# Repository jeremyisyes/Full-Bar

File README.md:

# Full-Bar
 40% keyboard with an encoder, full-sized shifts, full-sized enter, and a 10u spacebar.

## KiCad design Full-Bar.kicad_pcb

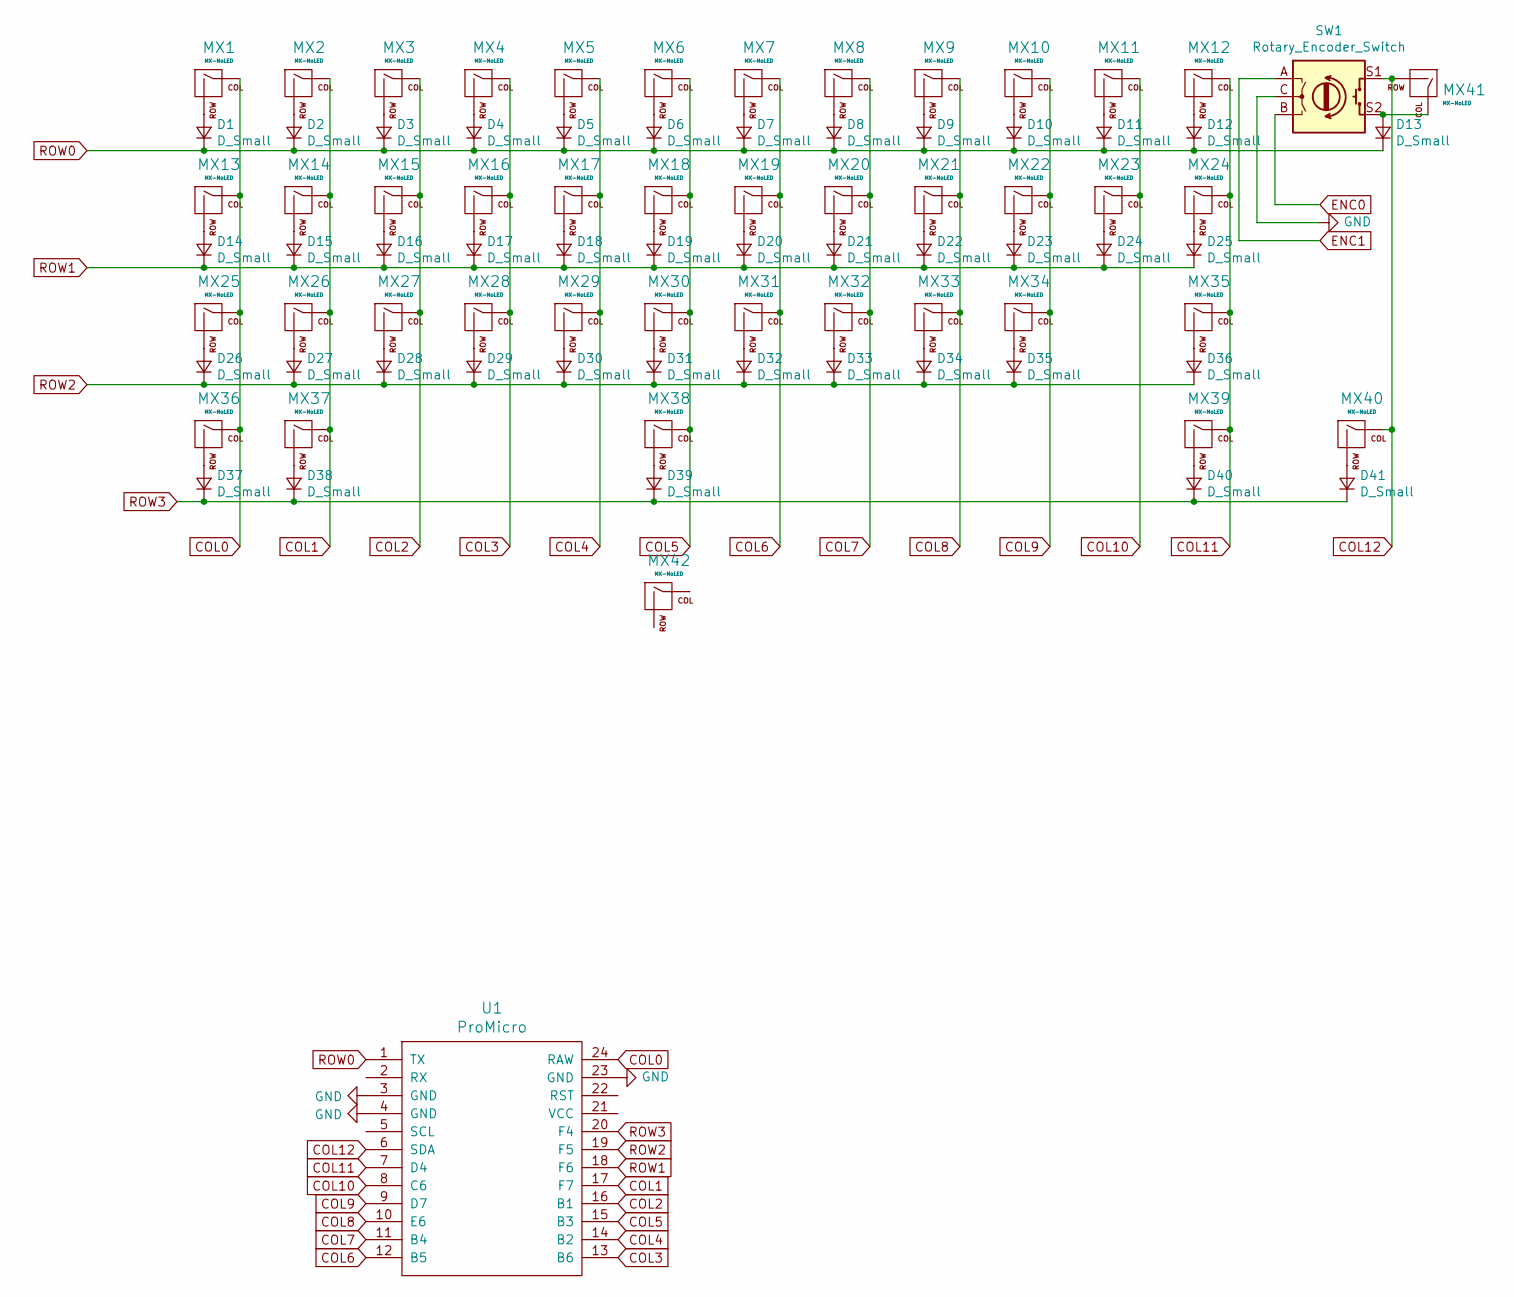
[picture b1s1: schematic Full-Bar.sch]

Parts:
D1, D2, D3, D4, D5, D6, D7, D8, D9, D10, D11, D12, D13, D14, D15, D16, D17, D18, D19, D20, D21, D22, D23, D24, D25, D26, D27, D28, D29, D30, D31, D32, D33, D34, D35, D36, D37, D38, D39, D40, D41: D_Small; D_A-405_P7.62mm_Horizontal
MX1, MX12: MX-NoLED; MX-1.5U-NoLED
MX2, MX3, MX4, MX5, MX6, MX7, MX8, MX9, MX10, MX11, MX14, MX15, MX16, MX17, MX18, MX19, MX20, MX21, MX22, MX23, MX26, MX27, MX28, MX29, MX30, MX31, MX32, MX33, MX34, MX36, MX37, MX39, MX40, MX41: MX-NoLED; MX-1U-NoLED
MX13: MX-NoLED; MX-1.75U-NoLED
MX24, MX25: MX-NoLED; MX-2.25U-NoLED
MX35: MX-NoLED; MX-2.75U-NoLED
MX38: MX-NoLED; MX-10U-ReversedStabilizers-NoLED
MX42: MX-NoLED; MX-7U-ReversedStabilizers-NoLED
SW1: Rotary_Encoder_Switch; RotaryEncoder_Alps_EC11E-Switch_Vertical_H20mm
U1: ProMicro

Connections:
COL0: MX1.1 (COL), MX13.1 (COL), MX25.1 (COL), MX36.1 (COL), U1.24 (RAW)
COL1: MX2.1 (COL), MX14.1 (COL), MX26.1 (COL), MX37.1 (COL), U1.17 (F7)
COL2: MX3.1 (COL), MX15.1 (COL), MX27.1 (COL), U1.16 (B1)
COL3: MX4.1 (COL), MX16.1 (COL), MX28.1 (COL), U1.13 (B6)
COL4: MX5.1 (COL), MX17.1 (COL), MX29.1 (COL), U1.14 (B2)
COL5: MX6.1 (COL), MX18.1 (COL), MX30.1 (COL), MX38.1 (COL), U1.15 (B3)
COL6: MX7.1 (COL), MX19.1 (COL), MX31.1 (COL), U1.12 (B5)
COL7: MX8.1 (COL), MX20.1 (COL), MX32.1 (COL), U1.11 (B4)
COL8: MX9.1 (COL), MX21.1 (COL), MX33.1 (COL), U1.10 (E6)
COL9: MX10.1 (COL), MX22.1 (COL), MX34.1 (COL), U1.9 (D7)
COL10: MX11.1 (COL), MX23.1 (COL), U1.8 (C6)
COL11: MX12.1 (COL), MX24.1 (COL), MX35.1 (COL), MX39.1 (COL), U1.7 (D4)
COL12: MX40.1 (COL), MX41.2 (ROW), SW1.S1, U1.6 (SDA)
GND: SW1.C, U1.3 (GND), U1.4 (GND), U1.23 (GND)
unnamed: D1.2 (A), MX1.2 (ROW)
unnamed: D2.2 (A), MX2.2 (ROW)
unnamed: D3.2 (A), MX3.2 (ROW)
unnamed: D4.2 (A), MX4.2 (ROW)
unnamed: D5.2 (A), MX5.2 (ROW)
unnamed: D6.2 (A), MX6.2 (ROW)
unnamed: D7.2 (A), MX7.2 (ROW)
unnamed: D8.2 (A), MX8.2 (ROW)
unnamed: D9.2 (A), MX9.2 (ROW)
unnamed: D10.2 (A), MX10.2 (ROW)
unnamed: D11.2 (A), MX11.2 (ROW)
unnamed: D12.2 (A), MX12.2 (ROW)
unnamed: D13.2 (A), MX41.1 (COL), SW1.S2
unnamed: D14.2 (A), MX13.2 (ROW)
unnamed: D15.2 (A), MX14.2 (ROW)
unnamed: D16.2 (A), MX15.2 (ROW)
unnamed: D17.2 (A), MX16.2 (ROW)
unnamed: D18.2 (A), MX17.2 (ROW)
unnamed: D19.2 (A), MX18.2 (ROW)
unnamed: D20.2 (A), MX19.2 (ROW)
unnamed: D21.2 (A), MX20.2 (ROW)
unnamed: D22.2 (A), MX21.2 (ROW)
unnamed: D23.2 (A), MX22.2 (ROW)
unnamed: D24.2 (A), MX23.2 (ROW)
unnamed: D25.2 (A), MX24.2 (ROW)
unnamed: D26.2 (A), MX25.2 (ROW)
unnamed: D27.2 (A), MX26.2 (ROW)
unnamed: D28.2 (A), MX27.2 (ROW)
unnamed: D29.2 (A), MX28.2 (ROW)
unnamed: D30.2 (A), MX29.2 (ROW)
unnamed: D31.2 (A), MX30.2 (ROW)
unnamed: D32.2 (A), MX31.2 (ROW)
unnamed: D33.2 (A), MX32.2 (ROW)
unnamed: D34.2 (A), MX33.2 (ROW)
unnamed: D35.2 (A), MX34.2 (ROW)
unnamed: D36.2 (A), MX35.2 (ROW)
unnamed: D37.2 (A), MX36.2 (ROW)
unnamed: D38.2 (A), MX37.2 (ROW)
unnamed: D39.2 (A), MX38.2 (ROW)
unnamed: D40.2 (A), MX39.2 (ROW)
unnamed: D41.2 (A), MX40.2 (ROW)
ROW0: D1.1 (K), D2.1 (K), D3.1 (K), D4.1 (K), D5.1 (K), D6.1 (K), D7.1 (K), D8.1 (K), D9.1 (K), D10.1 (K), D11.1 (K), D12.1 (K), D13.1 (K), U1.1 (TX)
ROW1: D14.1 (K), D15.1 (K), D16.1 (K), D17.1 (K), D18.1 (K), D19.1 (K), D20.1 (K), D21.1 (K), D22.1 (K), D23.1 (K), D24.1 (K), D25.1 (K), U1.18 (F6)
ROW2: D26.1 (K), D27.1 (K), D28.1 (K), D29.1 (K), D30.1 (K), D31.1 (K), D32.1 (K), D33.1 (K), D34.1 (K), D35.1 (K), D36.1 (K), U1.19 (F5)
ROW3: D37.1 (K), D38.1 (K), D39.1 (K), D40.1 (K), D41.1 (K), U1.20 (F4)

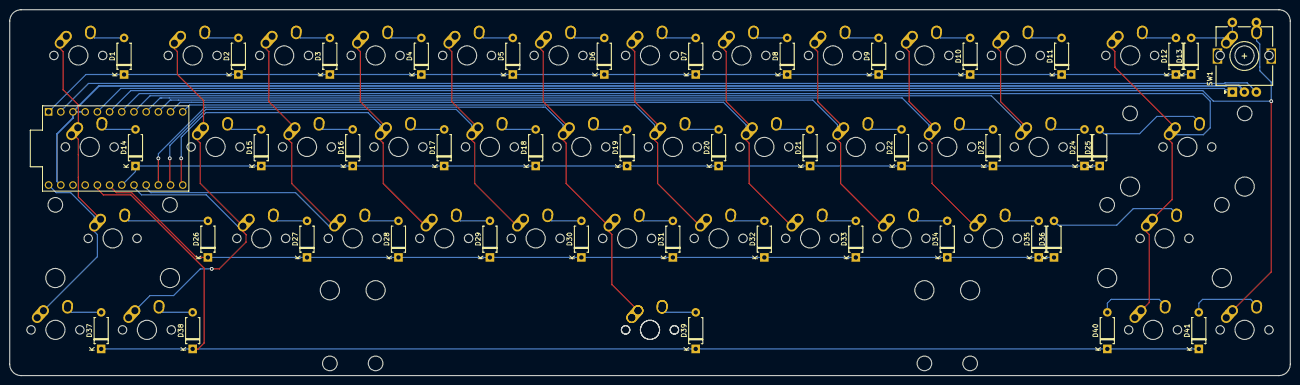
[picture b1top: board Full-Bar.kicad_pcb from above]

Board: 2 copper layers, 266.7 x 76.2 mm, 85 parts (1 on the bottom side), 59 nets.

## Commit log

2021-11-24 Initialize project
2021-11-24 Add submodules
2021-11-24 Add footprint libraries
2021-11-24 Schematic built
2021-11-24 Footprint assignments
2021-11-24 Pcb start
2021-11-24 Add 10u
2021-11-24 Finish layout minus pm
2021-11-25 Pm placed edges defined
2021-11-25 Starting traces
2021-11-26 Traces mostly finished minus one column
2021-11-28 traces ran
